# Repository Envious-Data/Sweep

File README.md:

# A fork of the Sweep V2 keyboard modified for MBUK

This fork is heavily modified and will not be firmware compatible with the original

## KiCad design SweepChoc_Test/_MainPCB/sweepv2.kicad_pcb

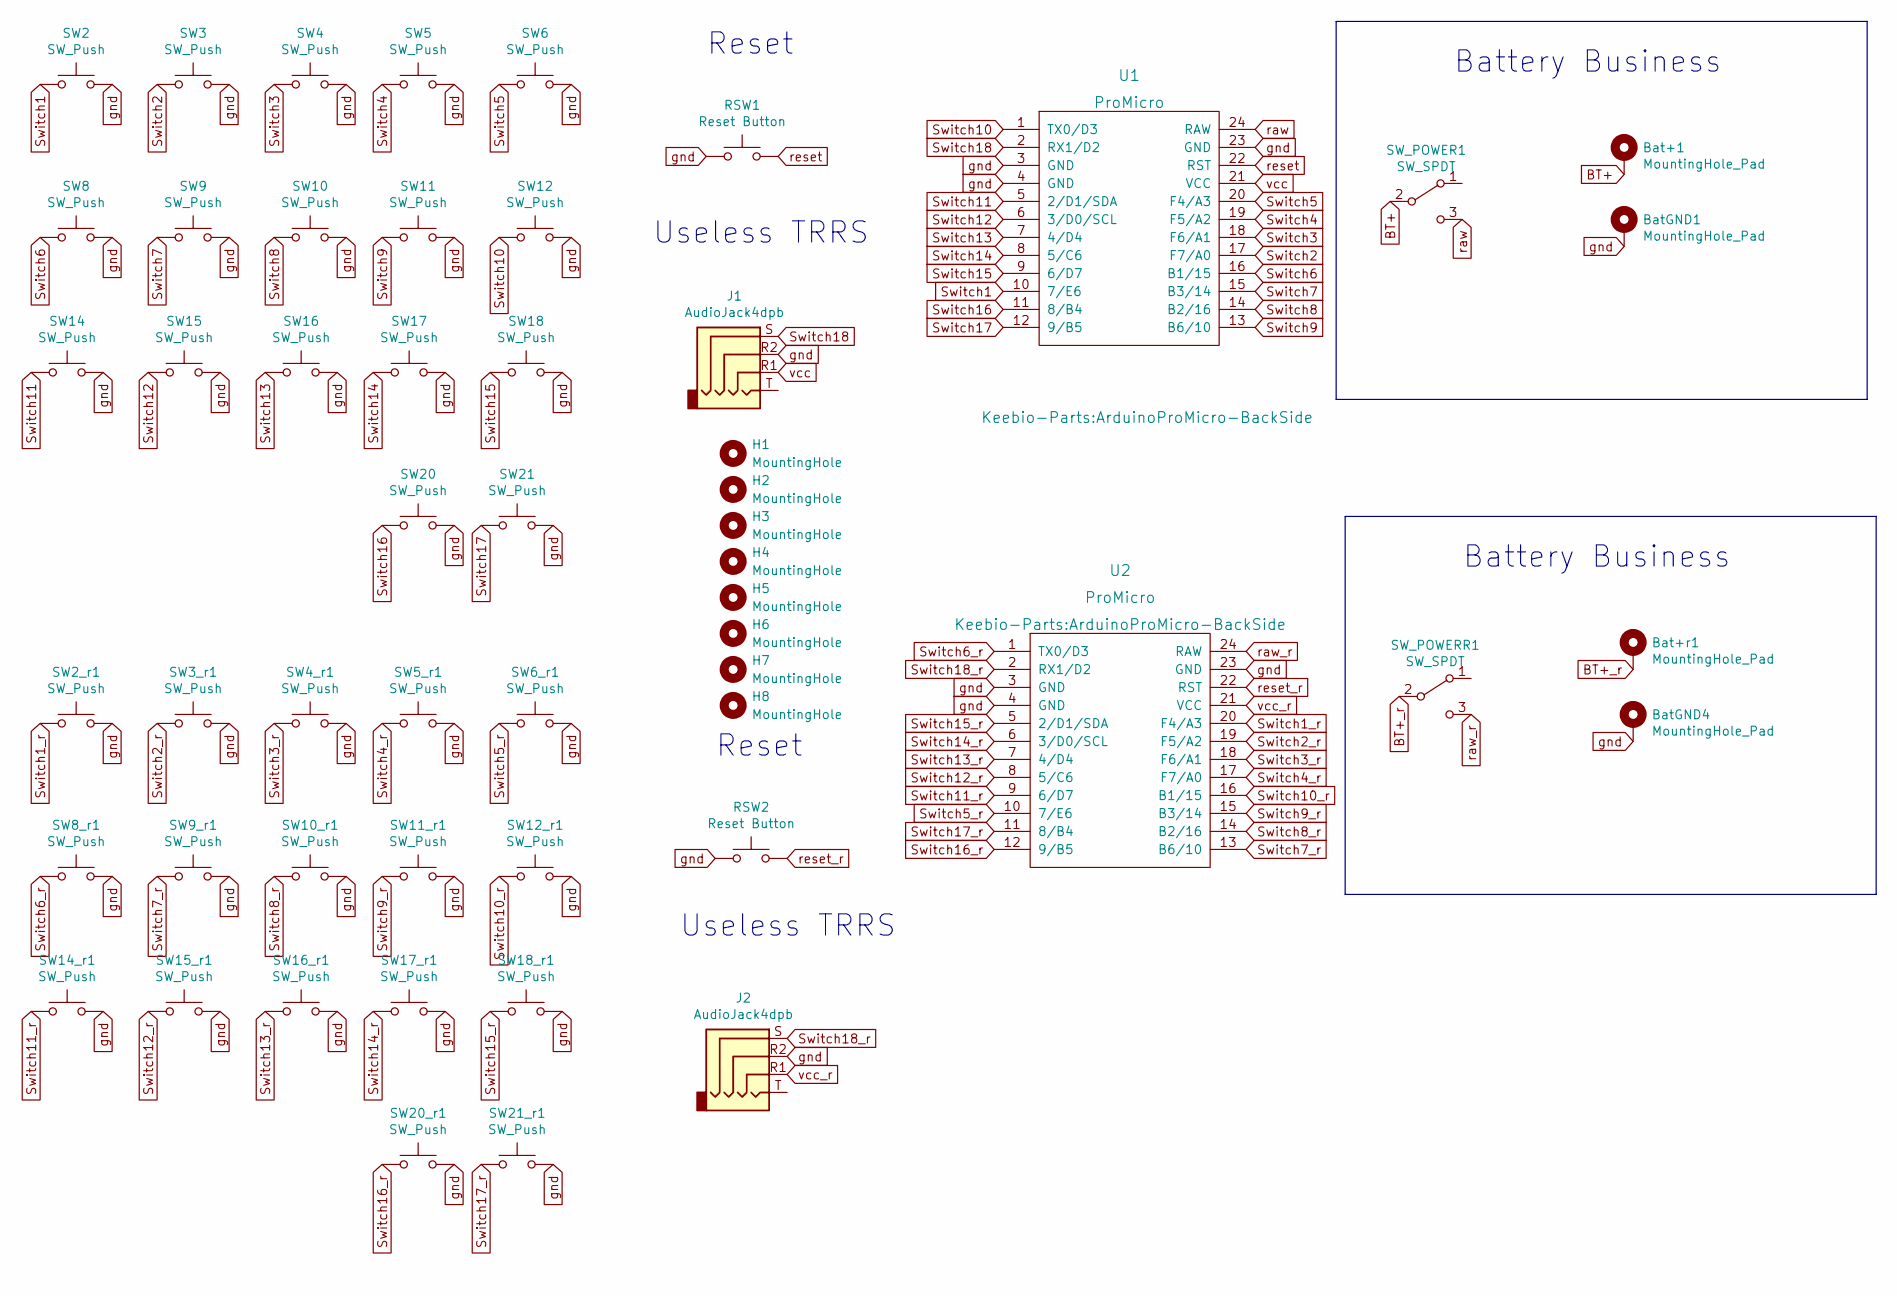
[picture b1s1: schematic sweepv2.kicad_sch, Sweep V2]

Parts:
Bat+1: MountingHole_Pad; Pin_D1.0mm_L10.0mm_LooseFit
Bat+r1: MountingHole_Pad; Pin_D1.0mm_L10.0mm_LooseFit
BatGND1, BatGND4: MountingHole_Pad; Pin_D1.0mm_L10.0mm_LooseFit
H1, H2, H3, H4, H5, H6, H7, H8: MountingHole; MountingHole_3.2mm_M3
J1, J2: AudioJack4dpb; PJ-320A
RSW1, RSW2: Reset Button; SW_Push_SPST_NO_Alps_SKRK
SW2, SW2_r1, SW3, SW3_r1, SW4, SW4_r1, SW5, SW5_r1, SW6, SW6_r1, SW8, SW8_r1, SW9, SW9_r1, SW10, SW10_r1, SW11, SW11_r1, SW12, SW12_r1, SW14, SW14_r1, SW15, SW15_r1, SW16, SW16_r1, SW17, SW17_r1, SW18, SW18_r1, SW20, SW20_r1, SW21, SW21_r1: SW_Push; SW_Kailh_Choc_V1
SW_POWER1: SW_SPDT; SW_SPDT_PCM12
SW_POWERR1: SW_SPDT; SW_SPDT_PCM12
U1, U2: ProMicro; ArduinoProMicro-BackSide

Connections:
BT+: Bat+1.1, SW_POWER1.2 (B)
BT+_r: Bat+r1.1, SW_POWERR1.2 (B)
Switch1: SW2.1, U1.10 (7/E6)
Switch1_r: SW2_r1.1, U2.20 (F4/A3)
Switch2: SW3.1, U1.17 (F7/A0)
Switch2_r: SW3_r1.1, U2.19 (F5/A2)
Switch3: SW4.1, U1.18 (F6/A1)
Switch3_r: SW4_r1.1, U2.18 (F6/A1)
Switch4: SW5.1, U1.19 (F5/A2)
Switch4_r: SW5_r1.1, U2.17 (F7/A0)
Switch5: SW6.1, U1.20 (F4/A3)
Switch5_r: SW6_r1.1, U2.10 (7/E6)
Switch6: SW8.1, U1.16 (B1/15)
Switch6_r: SW8_r1.1, U2.1 (TX0/D3)
Switch7: SW9.1, U1.15 (B3/14)
Switch7_r: SW9_r1.1, U2.13 (B6/10)
Switch8: SW10.1, U1.14 (B2/16)
Switch8_r: SW10_r1.1, U2.14 (B2/16)
Switch9: SW11.1, U1.13 (B6/10)
Switch9_r: SW11_r1.1, U2.15 (B3/14)
Switch10: SW12.1, U1.1 (TX0/D3)
Switch10_r: SW12_r1.1, U2.16 (B1/15)
Switch11: SW14.1, U1.5 (2/D1/SDA)
Switch11_r: SW14_r1.1, U2.9 (6/D7)
Switch12: SW15.1, U1.6 (3/D0/SCL)
Switch12_r: SW15_r1.1, U2.8 (5/C6)
Switch13: SW16.1, U1.7 (4/D4)
Switch13_r: SW16_r1.1, U2.7 (4/D4)
Switch14: SW17.1, U1.8 (5/C6)
Switch14_r: SW17_r1.1, U2.6 (3/D0/SCL)
Switch15: SW18.1, U1.9 (6/D7)
Switch15_r: SW18_r1.1, U2.5 (2/D1/SDA)
Switch16: SW20.1, U1.11 (8/B4)
Switch16_r: SW20_r1.1, U2.12 (9/B5)
Switch17: SW21.1, U1.12 (9/B5)
Switch17_r: SW21_r1.1, U2.11 (8/B4)
Switch18: J1.S, U1.2 (RX1/D2)
Switch18_r: J2.S, U2.2 (RX1/D2)
gnd: BatGND1.1, BatGND4.1, J1.R2, J2.R2, RSW1.1, RSW2.1, SW2.2, SW2_r1.2, SW3.2, SW3_r1.2, SW4.2, SW4_r1.2, SW5.2, SW5_r1.2, SW6.2, SW6_r1.2, SW8.2, SW8_r1.2, SW9.2, SW9_r1.2, SW10.2, SW10_r1.2, SW11.2, SW11_r1.2, SW12.2, SW12_r1.2, SW14.2, SW14_r1.2, SW15.2, SW15_r1.2, SW16.2, SW16_r1.2, SW17.2, SW17_r1.2, SW18.2, SW18_r1.2, SW20.2, SW20_r1.2, SW21.2, SW21_r1.2, U1.3 (GND), U1.4 (GND), U1.23 (GND), U2.3 (GND), U2.4 (GND), U2.23 (GND)
raw: SW_POWER1.3 (C), U1.24 (RAW)
raw_r: SW_POWERR1.3 (C), U2.24 (RAW)
reset: RSW1.2, U1.22 (RST)
reset_r: RSW2.2, U2.22 (RST)
vcc: J1.R1, U1.21 (VCC)
vcc_r: J2.R1, U2.21 (VCC)

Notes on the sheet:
Battery Business
Useless TRRS
Reset

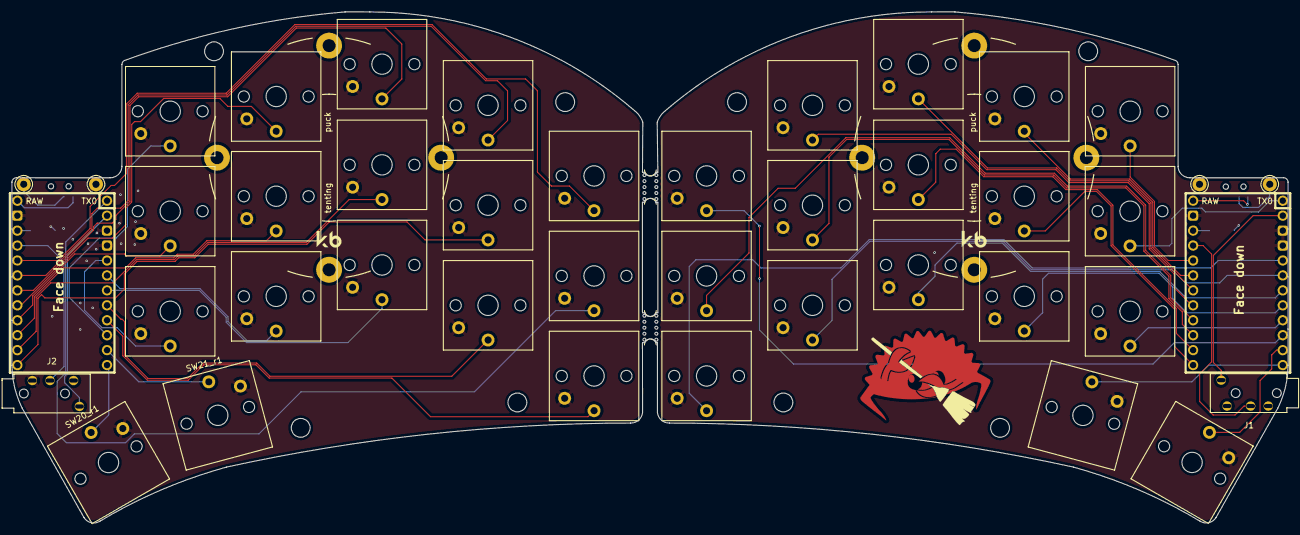
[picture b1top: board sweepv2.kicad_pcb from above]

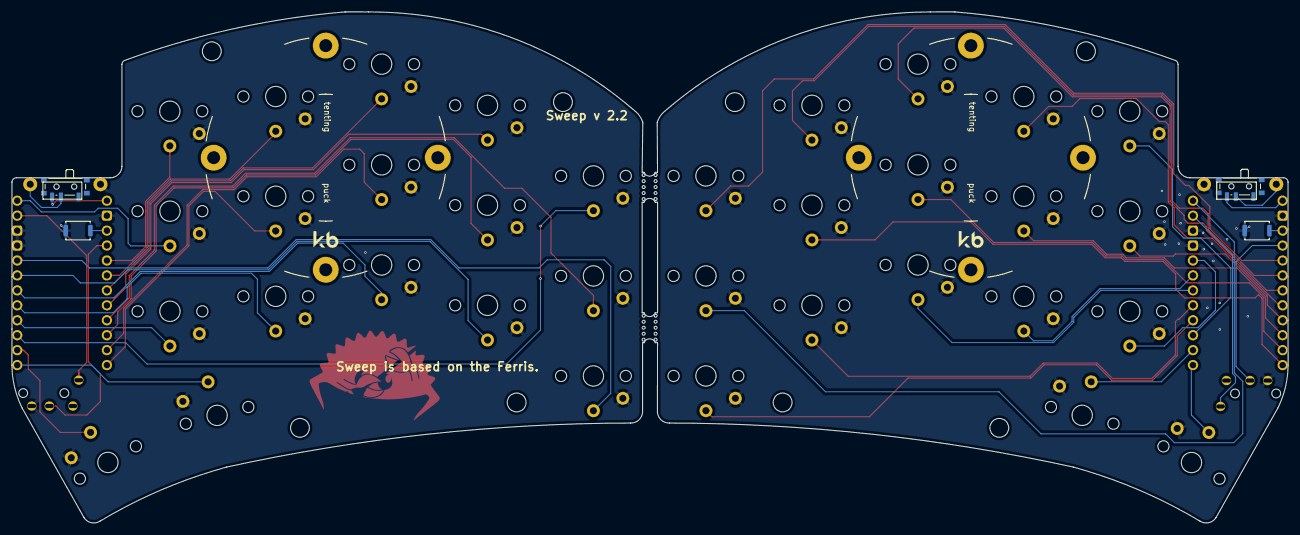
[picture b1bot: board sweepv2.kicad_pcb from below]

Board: 2 copper layers, 216.9 x 86.9 mm, 58 parts (6 on the bottom side), 45 nets.

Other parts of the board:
PUCK1, PUCK2: Tenting Puck; Tenting_Puck2
mouse-bite-2mm-slot-1, mouse-bite-2mm-slot-2: VAL**; mouse-bite-5mm-slot-with-space-for-track

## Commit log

2022-12-16 begining of overhaul for mbuk
2022-12-16 lots of worky
2022-12-16 renamed some files to be correct
2022-12-16 routed one trace nicer
2022-12-16 forgot to delete switgch plate form main PCB
2022-12-16 more missed corrections
2022-12-16 added logo on backplate
2022-12-16 some adjustments and stuff, changed my mind on some footprints and also missed some stuff I used for alignment and checking
2022-12-16 somehow some more things I missed, namely mount hole sizes
2022-12-17 rename of some bits and a couple missed fixes
2022-12-17 Generated Gerbers for all boards
2023-01-26 sorted schematic and PCB for MX ver
2023-01-26 re-worked choc version
2023-01-26 smol alignment fix
2023-01-28 made a test version, might succeed the main version eventually since it matches the pinout of the QMK PR
2023-02-02 routed all traces on MX version with matching pinout to PR
2023-02-02 created test version and matched schematic to QMK PR
2023-02-02 routed all traces
